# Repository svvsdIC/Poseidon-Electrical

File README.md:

# Poseidon-Electrical
Boards, files, and schematics for Poseidon
Notes:
  the Main Electronics Board is for the production version
  the Rapid_Prototype schematic is for the Rapid Prototype
  Turbidity sensor is a separate board used for the turbidity sensor.

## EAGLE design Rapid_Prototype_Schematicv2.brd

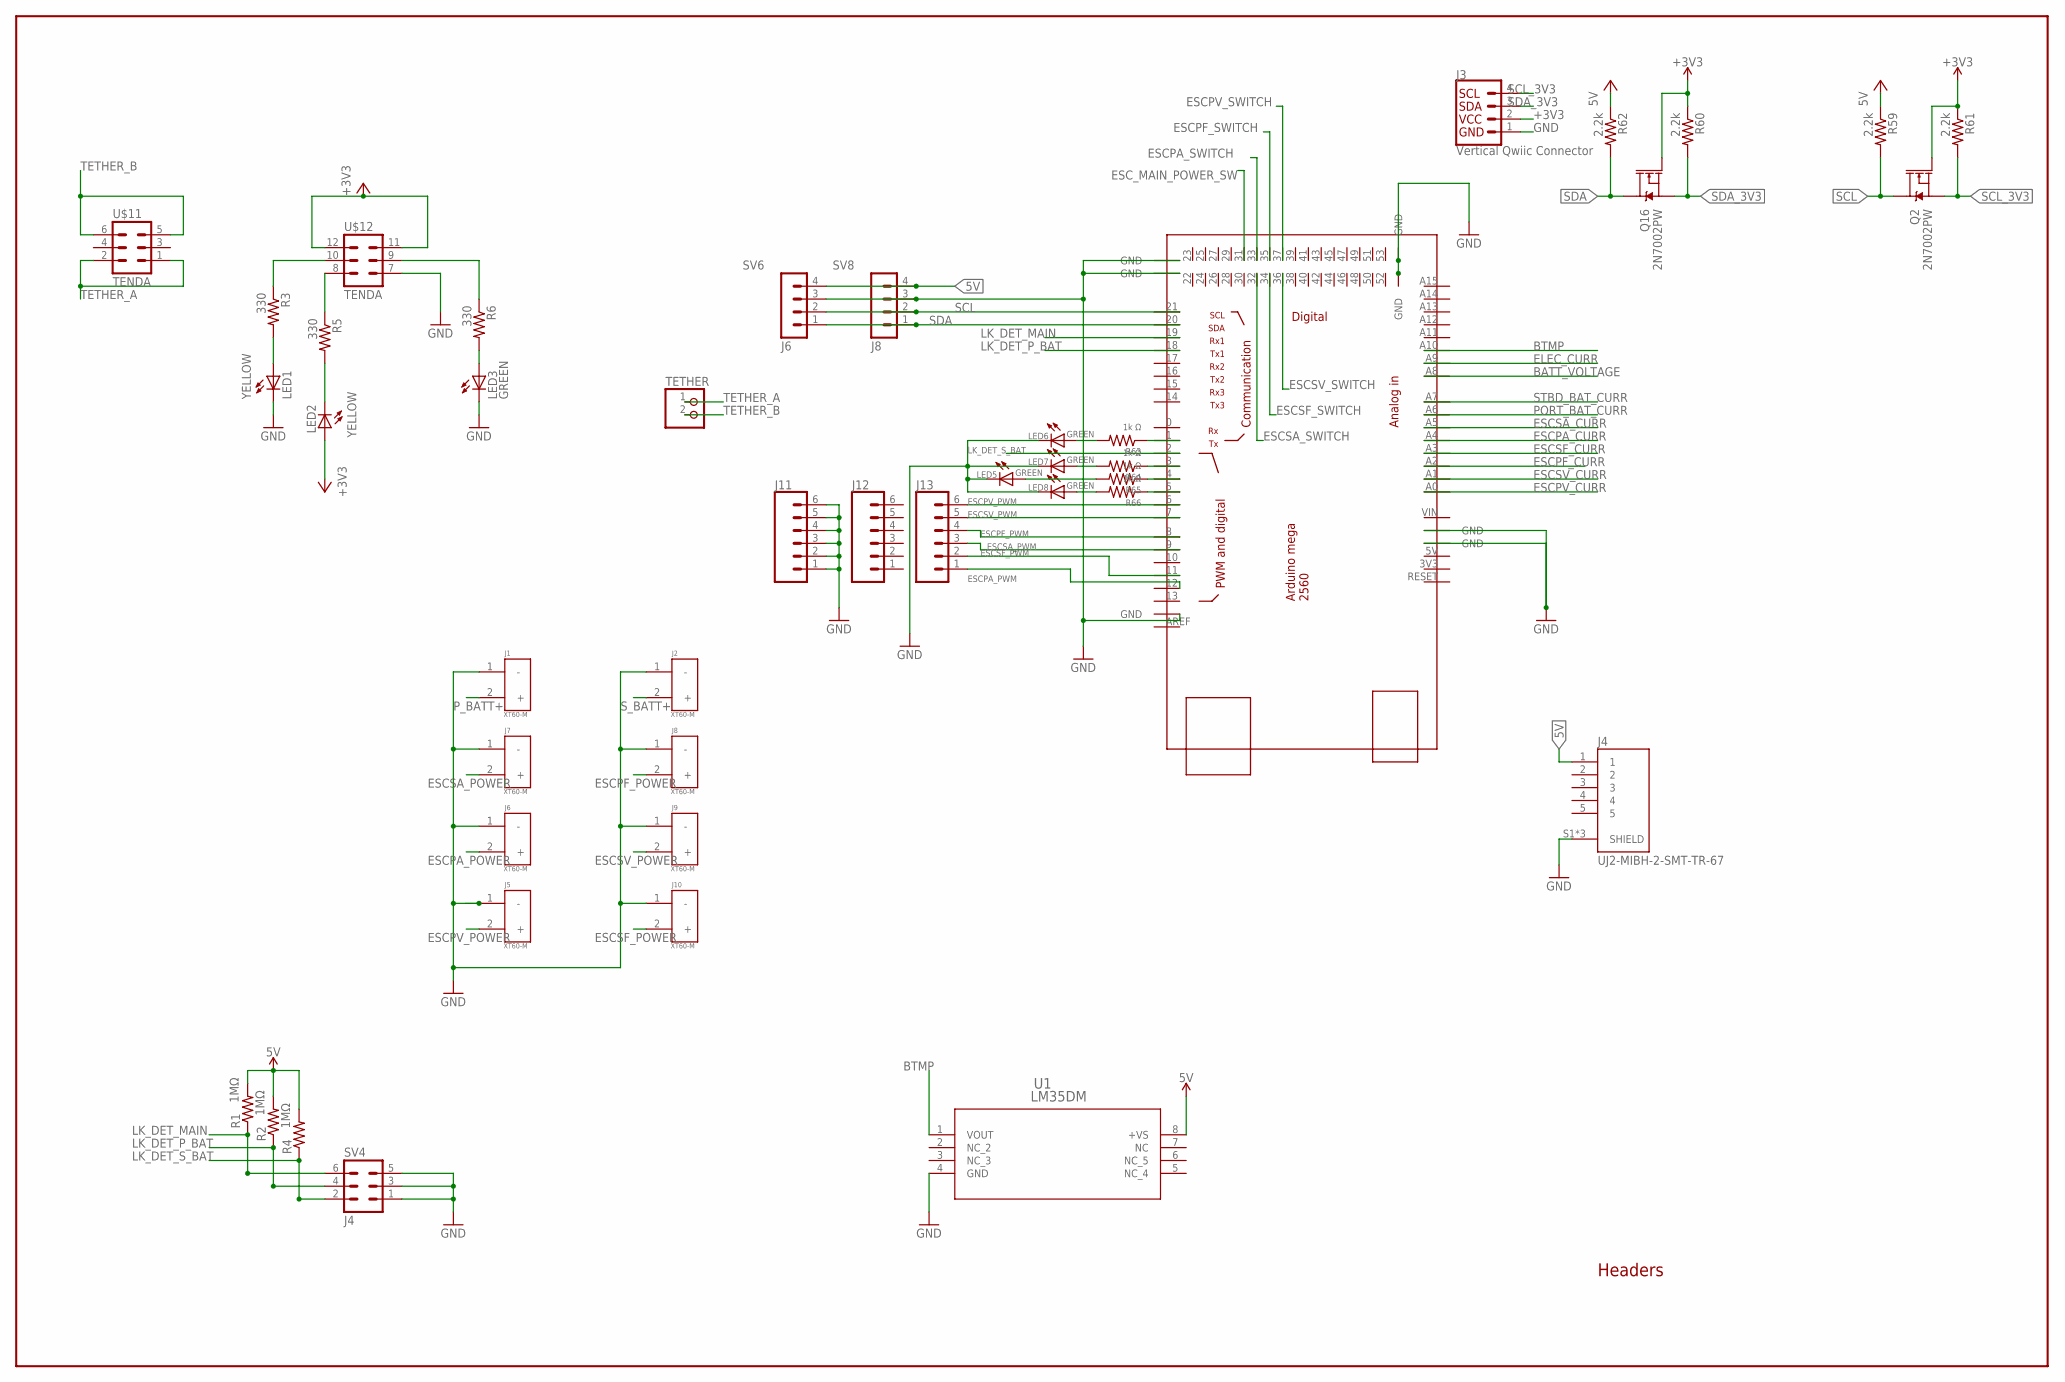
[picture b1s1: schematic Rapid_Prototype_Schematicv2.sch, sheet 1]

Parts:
$2_3_$_2020-06-04_21-52-10: MEGA_DEVICE; MEGAOUTLINE
J1, J2, J5, J6, J7, J8, J9, J10: XT60-M; AMASS_XT60-M
J3: Vertical Qwiic Connector; JST04_1MM_VERT
J4: UJ2-MIBH-2-SMT-TR-67; CUI_UJ2-MIBH-2-SMT-TR-67
J11, J12, J13: CONN_06SILK_FEMALE_PTH; 1X06
LED1, LED2: YELLOW; CHIPLED_0805
LED3, LED5, LED6, LED7, LED8: GREEN; CHIPLED_0805
Q2, Q16: 2N7002PW; SOT323
R1, R2, R4: 1MΩ; M0805
R3, R5, R6: 330; R0805
R59, R60, R61, R62: 2.2k; R0805
R63, R64, R65, R66: 1k Ω; M0805
SV4: J4; MA03-2
SV6: J6; MA04-1
SV8: J8; MA04-1
TETHER: PINHD-1X2; 1X02
U1: LM35DM; M08A
U$1: TENDA

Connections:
3.3V: Q2.1 (G), Q16.1 (G), R60.1, R61.1
5V: J4.1, R1.2, R2.2, R4.2, SV6.4, SV8.4, U1.8 (+VS); also elsewhere on the board
+3V3: J3.2, LED2.A, U$1.11 (5), U$1.12 (6); also elsewhere on the board
+5V: R59.1, R62.1
BATT_VOLTAGE: $2_3_$_2020-06-04_21-52-10.A8; also elsewhere on the board
BTMP: $2_3_$_2020-06-04_21-52-10.A10, U1.1 (VOUT)
ELEC_CURR: $2_3_$_2020-06-04_21-52-10.A9; also elsewhere on the board
ESCPA_CURR: $2_3_$_2020-06-04_21-52-10.A4; also elsewhere on the board
ESCPA_POWER: J6.2 (+); also elsewhere on the board
ESCPA_PWM: $2_3_$_2020-06-04_21-52-10.12, J13.1
ESCPA_SWITCH: $2_3_$_2020-06-04_21-52-10.33; also elsewhere on the board
ESCPF_CURR: $2_3_$_2020-06-04_21-52-10.A2; also elsewhere on the board
ESCPF_POWER: J8.2 (+); also elsewhere on the board
ESCPF_PWM: $2_3_$_2020-06-04_21-52-10.8, J13.4
ESCPF_SWITCH: $2_3_$_2020-06-04_21-52-10.35; also elsewhere on the board
ESCPV_CURR: $2_3_$_2020-06-04_21-52-10.A0; also elsewhere on the board
ESCPV_POWER: J5.2 (+); also elsewhere on the board
ESCPV_PWM: $2_3_$_2020-06-04_21-52-10.6, J13.6
ESCPV_SWITCH: $2_3_$_2020-06-04_21-52-10.37; also elsewhere on the board
ESCSA_CURR: $2_3_$_2020-06-04_21-52-10.A5; also elsewhere on the board
ESCSA_POWER: J7.2 (+); also elsewhere on the board
ESCSA_PWM: $2_3_$_2020-06-04_21-52-10.9, J13.3
ESCSA_SWITCH: $2_3_$_2020-06-04_21-52-10.32; also elsewhere on the board
ESCSF_CURR: $2_3_$_2020-06-04_21-52-10.A3; also elsewhere on the board
ESCSF_POWER: J10.2 (+); also elsewhere on the board
ESCSF_PWM: $2_3_$_2020-06-04_21-52-10.11, J13.2
ESCSF_SWITCH: $2_3_$_2020-06-04_21-52-10.34; also elsewhere on the board
ESCSV_CURR: $2_3_$_2020-06-04_21-52-10.A1; also elsewhere on the board
ESCSV_POWER: J9.2 (+); also elsewhere on the board
ESCSV_PWM: $2_3_$_2020-06-04_21-52-10.7, J13.5
ESCSV_SWITCH: $2_3_$_2020-06-04_21-52-10.36; also elsewhere on the board
ESC_MAIN_POWER_SW: $2_3_$_2020-06-04_21-52-10.31; also elsewhere on the board
GND: $2_3_$_2020-06-04_21-52-10.GND@1 (GND), $2_3_$_2020-06-04_21-52-10.GND@2 (GND), $2_3_$_2020-06-04_21-52-10.GND@3 (GND), $2_3_$_2020-06-04_21-52-10.GND@4 (GND), $2_3_$_2020-06-04_21-52-10.GND@5 (GND), $2_3_$_2020-06-04_21-52-10.GND@6 (GND), $2_3_$_2020-06-04_21-52-10.GND@7 (GND), J1.1 (-), J2.1 (-), J3.1, J4.S1 (SHIELD), J4.S2 (SHIELD), J4.S3 (SHIELD), J5.1 (-), J6.1 (-), J7.1 (-), J8.1 (-), J9.1 (-), J10.1 (-), J11.1, J11.2, J11.3, J11.4, J11.5, J11.6, LED1.C, LED3.C, LED5.C, LED6.C, LED7.C, LED8.C, SV4.1, SV4.3, SV4.5, SV6.3, SV8.3, U1.4 (GND), U$1.7 (1); also elsewhere on the board
LK_DET_MAIN: $2_3_$_2020-06-04_21-52-10.19, R1.1, SV4.6
LK_DET_P_BAT: $2_3_$_2020-06-04_21-52-10.18, R2.1, SV4.4
LK_DET_S_BAT: $2_3_$_2020-06-04_21-52-10.2, R4.1, SV4.2
unnamed: $2_3_$_2020-06-04_21-52-10.3, R64.1
unnamed: $2_3_$_2020-06-04_21-52-10.4, R65.1
unnamed: $2_3_$_2020-06-04_21-52-10.5, R66.1
unnamed: $2_3_$_2020-06-04_21-52-10.1, R63.1
unnamed: LED6.A, R63.2
unnamed: LED7.A, R64.2
unnamed: LED5.A, R65.2
unnamed: LED8.A, R66.2
unnamed: R3.1, U$1.10 (4)
unnamed: LED2.C, R5.2
unnamed: R5.1, U$1.8 (2)
unnamed: LED1.A, R3.2
unnamed: R6.1, U$1.9 (3)
unnamed: LED3.A, R6.2
PORT_BAT_CURR: $2_3_$_2020-06-04_21-52-10.A6; also elsewhere on the board
P_BATT+: J1.2 (+); also elsewhere on the board
SCL: $2_3_$_2020-06-04_21-52-10.21, Q2.3 (D), R59.2, SV6.2, SV8.2
SCL_3V3: J3.4, Q2.2 (S), R61.2
SDA: $2_3_$_2020-06-04_21-52-10.20, Q16.3 (D), R62.2, SV6.1, SV8.1
SDA_3V3: J3.3, Q16.2 (S), R60.2
STBD_BAT_CURR: $2_3_$_2020-06-04_21-52-10.A7; also elsewhere on the board
S_BATT+: J2.2 (+); also elsewhere on the board
TETHER_A: TETHER.1, U$1.1, U$1.2; also elsewhere on the board
TETHER_B: TETHER.2, U$1.5, U$1.6; also elsewhere on the board

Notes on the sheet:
Headers

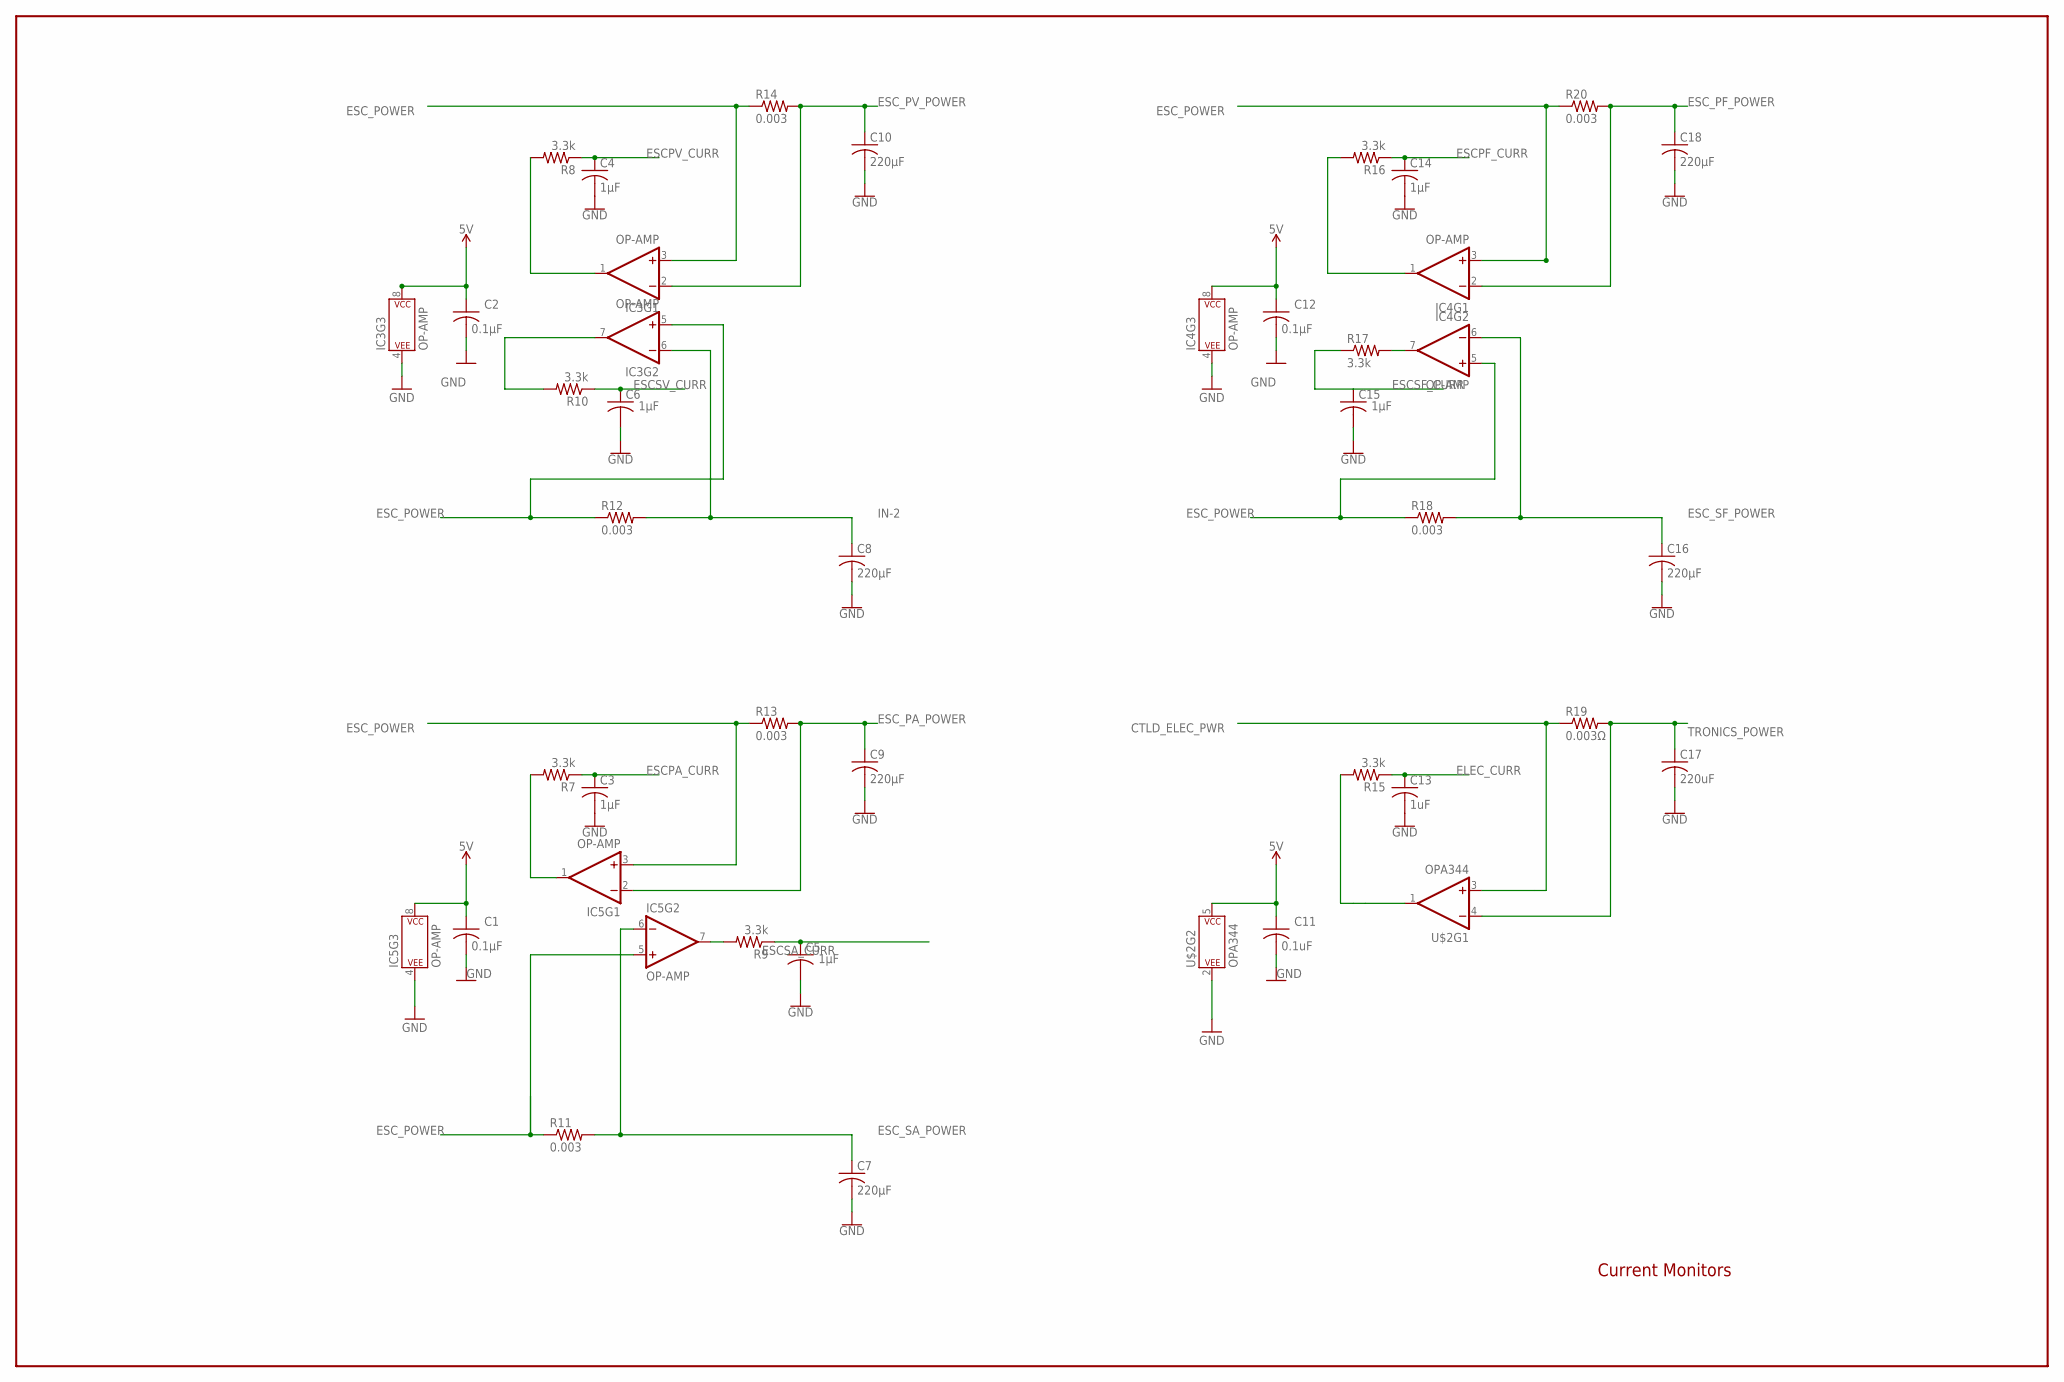
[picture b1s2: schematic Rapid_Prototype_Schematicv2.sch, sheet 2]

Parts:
C1, C2, C12: 0.1µF; C0603
C3, C4, C5, C6, C14, C15: 1µF; C0603
C7, C8, C9, C10, C16, C18: 220µF; 3.5MMCAP
C11: 0.1uF; C0603
C13: 1uF; C0805
C17: 220uF; 3.5MMCAP
IC3, IC4, IC5: OP-AMP; DIP08
R7, R8, R9, R10, R15, R16, R17: 3.3k; R0603
R11, R12, R13, R14, R18, R20: 0.003; R1206
R19: 0.003Ω; R1206
U$2: OPA344; SOT23-5

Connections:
5V: C1.1, C2.1, C11.1, C12.1, IC3.8 (P$V+), IC4.8 (P$V+), IC5.8 (P$V+), U$2.5 (P$V+); also elsewhere on the board
CTLD_ELEC_PWR: R19.1, U$2.3 (+IN); also elsewhere on the board
ELEC_CURR: C13.1, R15.1; also elsewhere on the board
ESCPA_CURR: C3.1, R7.1; also elsewhere on the board
ESCPF_CURR: C14.1, R16.1; also elsewhere on the board
ESCPV_CURR: C4.1, R8.1; also elsewhere on the board
ESCSA_CURR: C5.1, R9.1; also elsewhere on the board
ESCSF_CURR: C15.1, R17.1; also elsewhere on the board
ESCSV_CURR: C6.1, R10.1; also elsewhere on the board
ESC_PA_POWER: C9.1, IC5.2 (-IN), R13.2; also elsewhere on the board
ESC_PF_POWER: C18.1, IC4.2 (-IN), R20.2; also elsewhere on the board
ESC_POWER: IC3.3 (+IN), IC3.5 (+IN), IC4.3 (+IN), IC4.5 (+IN), IC5.3 (+IN), IC5.5 (+IN), R11.1, R12.1, R13.1, R14.1, R18.1, R20.1; also elsewhere on the board
ESC_PV_POWER: C10.1, IC3.2 (-IN), R14.2; also elsewhere on the board
ESC_SA_POWER: C7.1, IC5.6 (-IN), R11.2; also elsewhere on the board
ESC_SF_POWER: C16.1, IC4.6 (-IN), R18.2; also elsewhere on the board
GND: C1.2, C2.2, C3.2, C4.2, C5.2, C6.2, C7.2, C8.2, C9.2, C10.2, C11.2, C12.2, C13.2, C14.2, C15.2, C16.2, C17.2, C18.2, IC3.4 (P$V-), IC4.4 (P$V-), IC5.4 (P$V-), U$2.2 (P$V-); also elsewhere on the board
IN-2: C8.1, IC3.6 (-IN), R12.2
unnamed: IC4.1 (OUT), R16.2
unnamed: IC4.7 (OUT), R17.2
unnamed: IC5.1 (OUT), R7.2
unnamed: IC5.7 (OUT), R9.2
unnamed: R15.2, U$2.1 (OUT)
O: IC3.1 (OUT), R8.2
O2: IC3.7 (OUT), R10.2
TRONICS_POWER: C17.1, R19.2, U$2.4 (-IN); also elsewhere on the board

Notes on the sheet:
Current Monitors

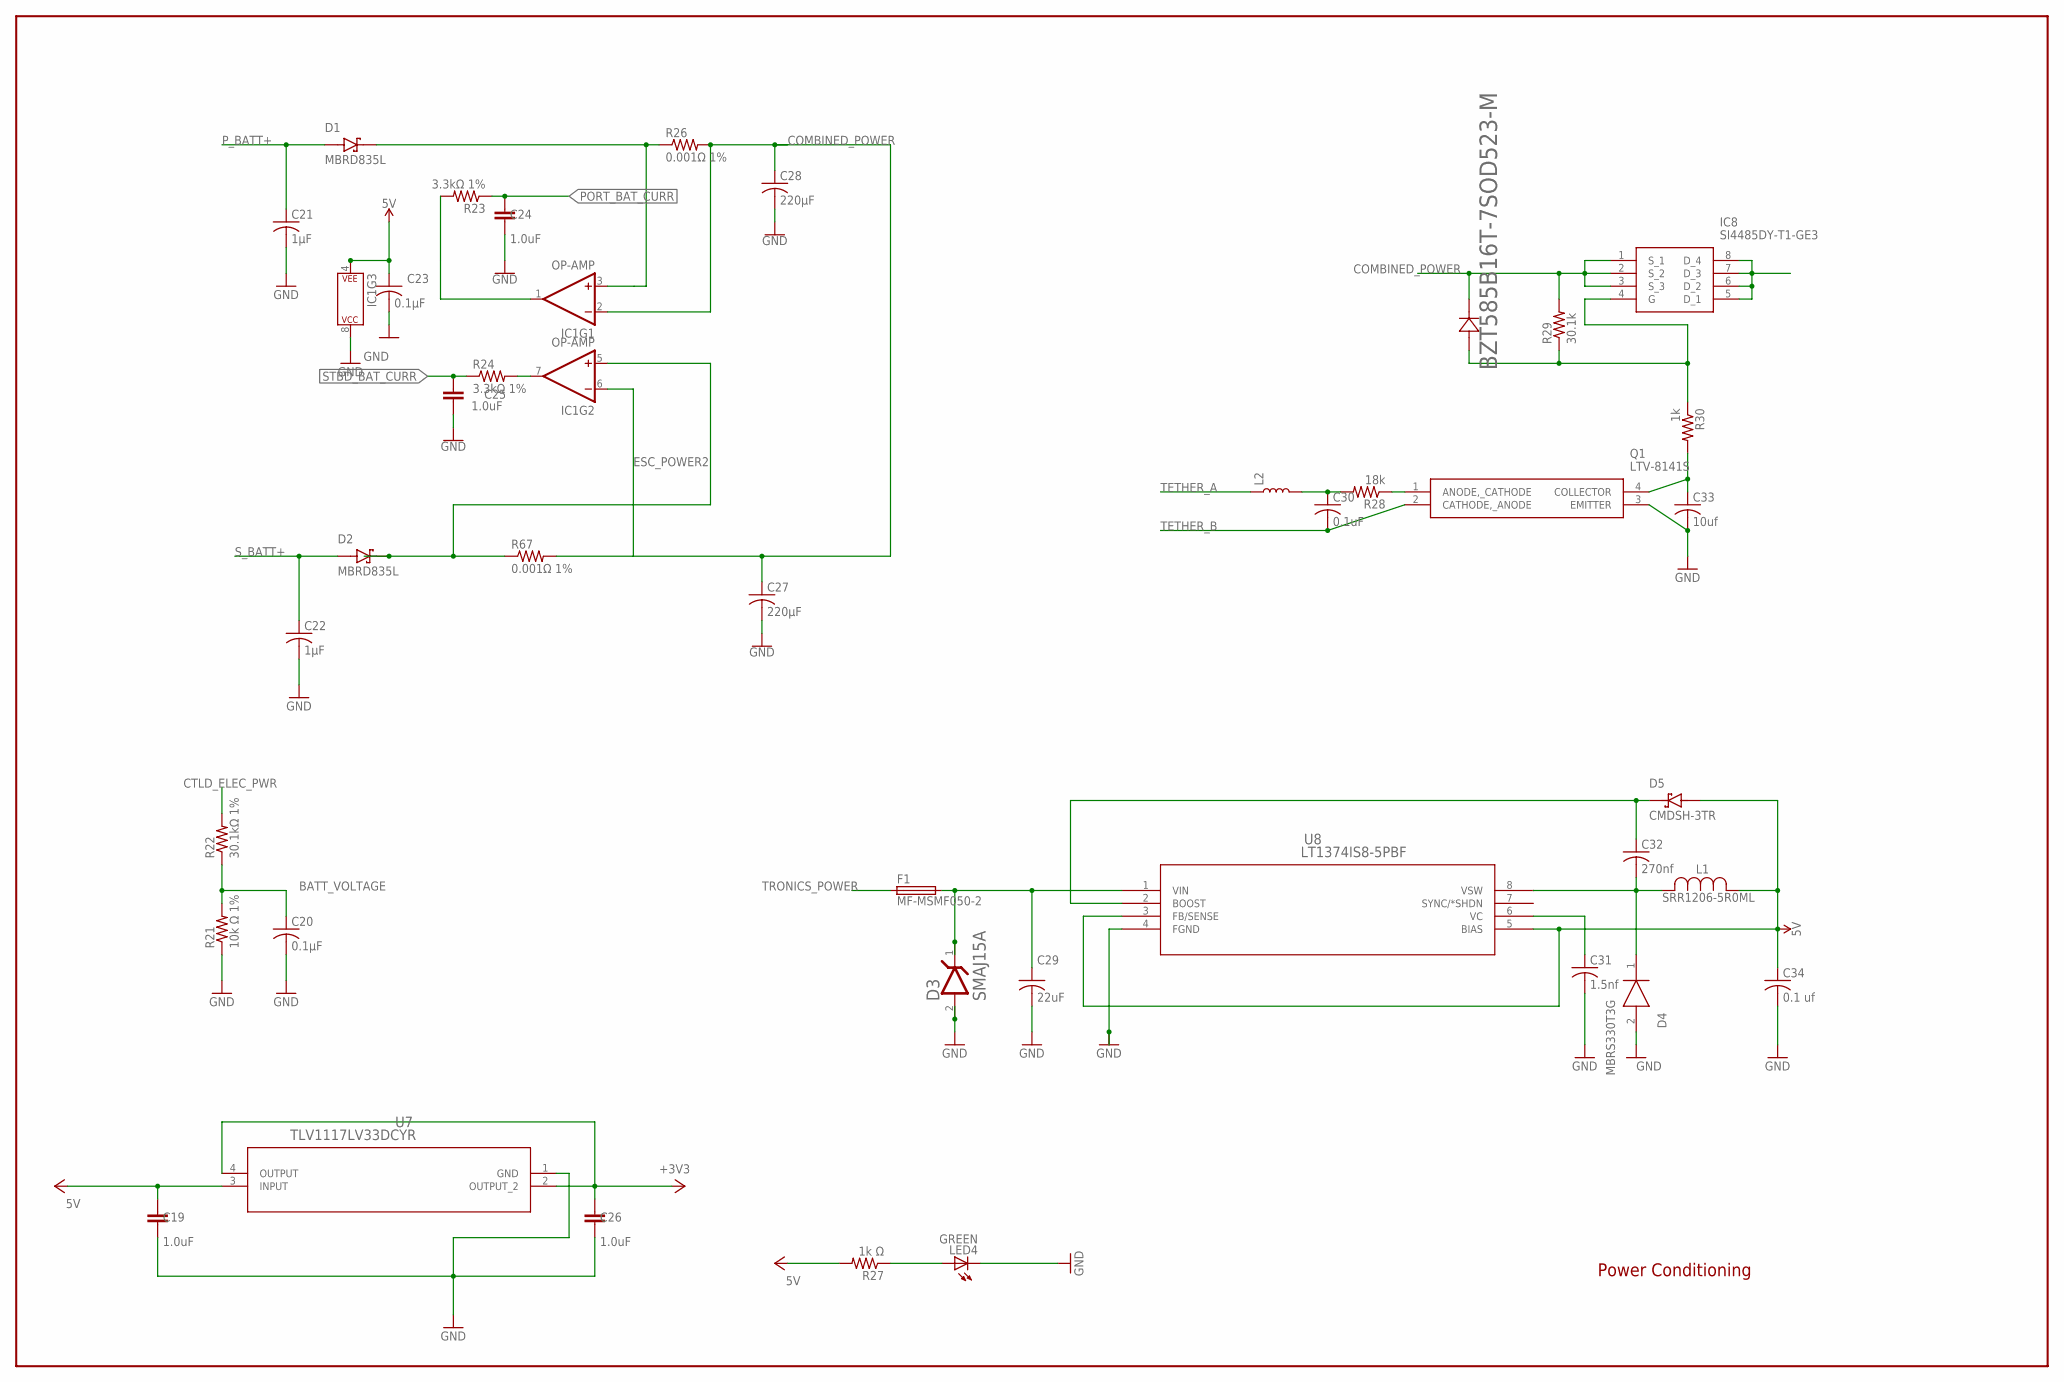
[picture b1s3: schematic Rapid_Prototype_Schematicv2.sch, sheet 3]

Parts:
C19, C24, C25, C26: 1.0uF; 0603
C20, C23: 0.1µF; C0603
C21, C22: 1µF; C0603
C27, C28: 220µF; 3.5MMCAP
C29: 22uF; C1206
C30: 0.1uF; C0603
C31: 1.5nf; C1206
C32: 270nf; C0603
C33: 10uf; C0603
C34: 0.1 uf; C0603
CR1: BZT585B16T-7SOD523-M; SOD523-M
D1, D2: MBRD835L; DPAK229P990X238-3N
D3: BOURNS-INC.---SMAJ15A_BOURNS_INC._SMAJ15ABOURNS_I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; BOURNS-INC.---SMAJ15A_BOURNS_INC._SMAJ15A_0
D4: MBRS330T3G; DIOM7958X256N
D5: CMDSH-3TR; SOD2512X110N
F1: MF-MSMF050-2; FUSM1812X02
IC1: OP-AMP; DIP08
IC8: SI4485DY-T1-GE3; SOIC127P600X175-8N
L1: SRR1206-5R0ML; IND_BOURNS_SRR1240
L2: INDUCTOR; XFL4020
LED4: GREEN; CHIPLED_0805
Q1: LTV-8141S; SOP254P1016X460-4N
R21: 10k Ω 1%; M0805
R22: 30.1kΩ 1%; M0805
R23, R24: 3.3kΩ 1%; R0603
R26, R67: 0.001Ω 1%; R2512
R27: 1k Ω; M0805
R28: 18k; M0805
R29: 30.1k; M0805
R30: 1k; M0805
U7: TLV1117LV33DCYR; DCY4
U8: LT1374IS8-5PBF; SO-8_S

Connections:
5V: C19.1, C23.1, C34.1, D5.A, IC1.4 (P$V-), L1.1, R27.2, U7.3 (INPUT), U8.3 (FB/SENSE), U8.5 (BIAS); also elsewhere on the board
+3V3: C26.1, U7.2 (OUTPUT_2), U7.4 (OUTPUT); also elsewhere on the board
BATT_VOLTAGE: C20.1, R21.2, R22.1; also elsewhere on the board
COMBINED_POWER: C27.1, C28.1, CR1.1, IC1.2 (-IN), IC1.6 (-IN), IC8.1 (S_1), IC8.2 (S_2), IC8.3 (S_3), R26.2, R29.2, R67.2; also elsewhere on the board
CTLD_ELEC_PWR: IC8.5 (D_1), IC8.6 (D_2), IC8.7 (D_3), IC8.8 (D_4), R22.2; also elsewhere on the board
ESC_POWER1: D1.4 (K), IC1.3 (+IN), R26.1
ESC_POWER2: D2.4 (K), IC1.5 (+IN), R67.1
GND: C19.2, C20.2, C21.2, C22.2, C23.2, C24.2, C25.2, C26.2, C27.2, C28.2, C29.2, C31.2, C33.2, C34.2, D3.2 (ANODE), D4.2 (A), IC1.8 (P$V+), LED4.C, Q1.3 (EMITTER), R21.1, U7.1 (GND), U8.4 (FGND); also elsewhere on the board
unnamed: C32.2, D4.1 (K), L1.2, U8.8 (VSW)
unnamed: C31.1, U8.6 (VC)
unnamed: Q1.1 (ANODE,_CATHODE), R28.1
unnamed: IC1.1 (OUT), R23.2
unnamed: IC1.7 (OUT), R24.2
unnamed: C29.1, D3.1 (CATHODE), F1.2, U8.1 (VIN)
unnamed: C32.1, D5.C, U8.2 (BOOST)
unnamed: LED4.A, R27.1
unnamed: CR1.2, IC8.4 (G), R29.1, R30.1
unnamed: C33.1, Q1.4 (COLLECTOR), R30.2
unnamed: C30.1, L2.P$2 (2), R28.2
PORT_BAT_CURR: C24.1, R23.1; also elsewhere on the board
P_BATT+: C21.1, D1.1 (A), D1.3 (A); also elsewhere on the board
STBD_BAT_CURR: C25.1, R24.1; also elsewhere on the board
S_BATT+: C22.1, D2.1 (A), D2.3 (A); also elsewhere on the board
TETHER_A: L2.P$1 (1); also elsewhere on the board
TETHER_B: C30.2, Q1.2 (CATHODE,_ANODE); also elsewhere on the board
TRONICS_POWER: F1.1; also elsewhere on the board

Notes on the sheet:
Power Conditioning

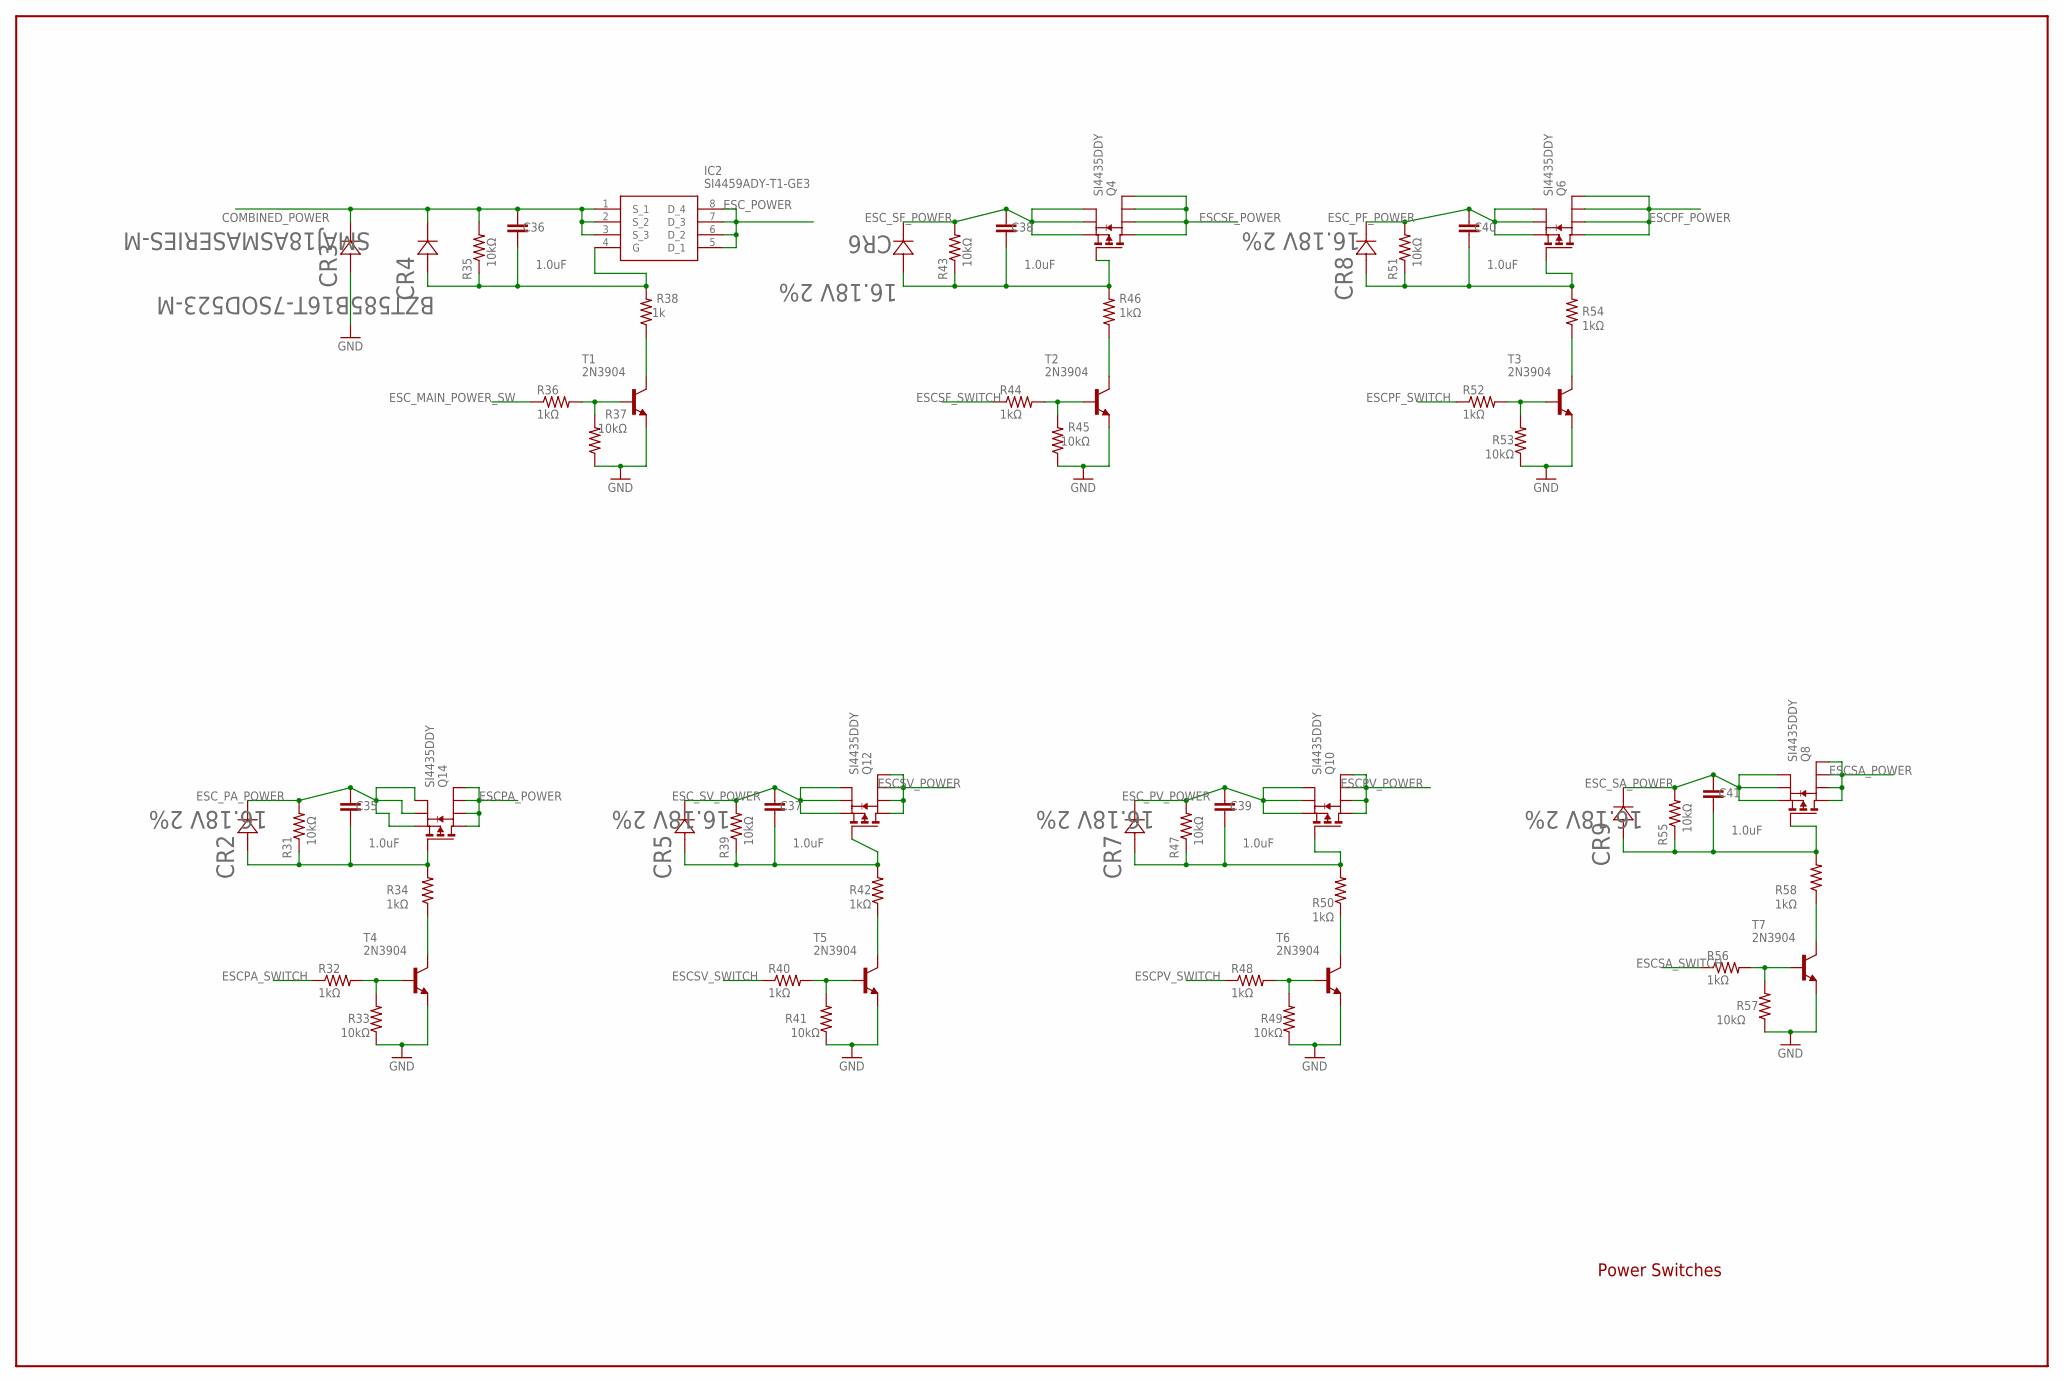
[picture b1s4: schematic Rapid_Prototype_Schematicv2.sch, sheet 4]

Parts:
C35, C36, C37, C38, C39, C40, C41: 1.0uF; 0603
CR2, CR5, CR6, CR7, CR8, CR9: 16.18V 2%; SOD523-M
CR3: SMAJ18ASMASERIES-M; SMASERIES-M
CR4: BZT585B16T-7SOD523-M; SOD523-M
IC2: SI4459ADY-T1-GE3; SOIC127P600X175-8N
Q4, Q6, Q8, Q10, Q12, Q14: SI4435DDY; SO-8
R31, R33, R35, R37, R39, R41, R43, R45, R47, R49, R51, R53, R55, R57: 10kΩ; R0603
R32, R34, R36, R40, R42, R44, R46, R48, R50, R52, R54, R56, R58: 1kΩ; R0603
R38: 1k; R0603
T1, T2, T3, T4, T5, T6, T7: 2N3904; TO92

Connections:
COMBINED_POWER: C36.1, CR3.1, CR4.1, IC2.1 (S_1), IC2.2 (S_2), IC2.3 (S_3), R35.2; also elsewhere on the board
ESCPA_POWER: Q14.5 (D), Q14.6 (D), Q14.7 (D), Q14.8 (D); also elsewhere on the board
ESCPA_SWITCH: R32.1; also elsewhere on the board
ESCPF_POWER: Q6.5 (D), Q6.6 (D), Q6.7 (D), Q6.8 (D); also elsewhere on the board
ESCPF_SWITCH: R52.1; also elsewhere on the board
ESCPV_POWER: Q10.5 (D), Q10.6 (D), Q10.7 (D), Q10.8 (D); also elsewhere on the board
ESCPV_SWITCH: R48.1; also elsewhere on the board
ESCSA_POWER: Q8.5 (D), Q8.6 (D), Q8.7 (D), Q8.8 (D); also elsewhere on the board
ESCSA_SWITCH: R56.1; also elsewhere on the board
ESCSF_POWER: Q4.5 (D), Q4.6 (D), Q4.7 (D), Q4.8 (D); also elsewhere on the board
ESCSF_SWITCH: R44.1; also elsewhere on the board
ESCSV_POWER: Q12.5 (D), Q12.6 (D), Q12.7 (D), Q12.8 (D); also elsewhere on the board
ESCSV_SWITCH: R40.1; also elsewhere on the board
ESC_MAIN_POWER_SW: R36.1; also elsewhere on the board
ESC_PA_POWER: C35.1, CR2.1, Q14.1 (S), Q14.2 (S), Q14.3 (S), R31.2; also elsewhere on the board
ESC_PF_POWER: C40.1, CR8.1, Q6.1 (S), Q6.2 (S), Q6.3 (S), R51.2; also elsewhere on the board
ESC_POWER: IC2.5 (D_1), IC2.6 (D_2), IC2.7 (D_3), IC2.8 (D_4); also elsewhere on the board
ESC_PV_POWER: C39.1, CR7.1, Q10.1 (S), Q10.2 (S), Q10.3 (S), R47.2; also elsewhere on the board
ESC_SA_POWER: C41.1, CR9.1, Q8.1 (S), Q8.2 (S), Q8.3 (S), R55.2; also elsewhere on the board
ESC_SF_POWER: C38.1, CR6.1, Q4.1 (S), Q4.2 (S), Q4.3 (S), R43.2; also elsewhere on the board
ESC_SV_POWER: C37.1, CR5.1, Q12.1 (S), Q12.2 (S), Q12.3 (S), R39.2
GND: CR3.2, R33.1, R37.1, R41.1, R45.1, R49.1, R53.1, R57.1, T1.3 (E), T2.3 (E), T3.3 (E), T4.3 (E), T5.3 (E), T6.3 (E), T7.3 (E); also elsewhere on the board
unnamed: C36.2, CR4.2, IC2.4 (G), R35.1, R38.2
unnamed: R32.2, R33.2, T4.2 (B)
unnamed: C40.2, CR8.2, Q6.4 (G), R51.1, R54.2
unnamed: C35.2, CR2.2, Q14.4 (G), R31.1, R34.2
unnamed: R38.1, T1.1 (C)
unnamed: R36.2, R37.2, T1.2 (B)
unnamed: R34.1, T4.1 (C)
unnamed: C37.2, CR5.2, Q12.4 (G), R39.1, R42.2
unnamed: R40.2, R41.2, T5.2 (B)
unnamed: R42.1, T5.1 (C)
unnamed: C39.2, CR7.2, Q10.4 (G), R47.1, R50.2
unnamed: R48.2, R49.2, T6.2 (B)
unnamed: R50.1, T6.1 (C)
unnamed: C41.2, CR9.2, Q8.4 (G), R55.1, R58.2
unnamed: R56.2, R57.2, T7.2 (B)
unnamed: R58.1, T7.1 (C)
unnamed: R52.2, R53.2, T3.2 (B)
unnamed: R54.1, T3.1 (C)
unnamed: C38.2, CR6.2, Q4.4 (G), R43.1, R46.2
unnamed: R44.2, R45.2, T2.2 (B)
unnamed: R46.1, T2.1 (C)

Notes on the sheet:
Power Switches

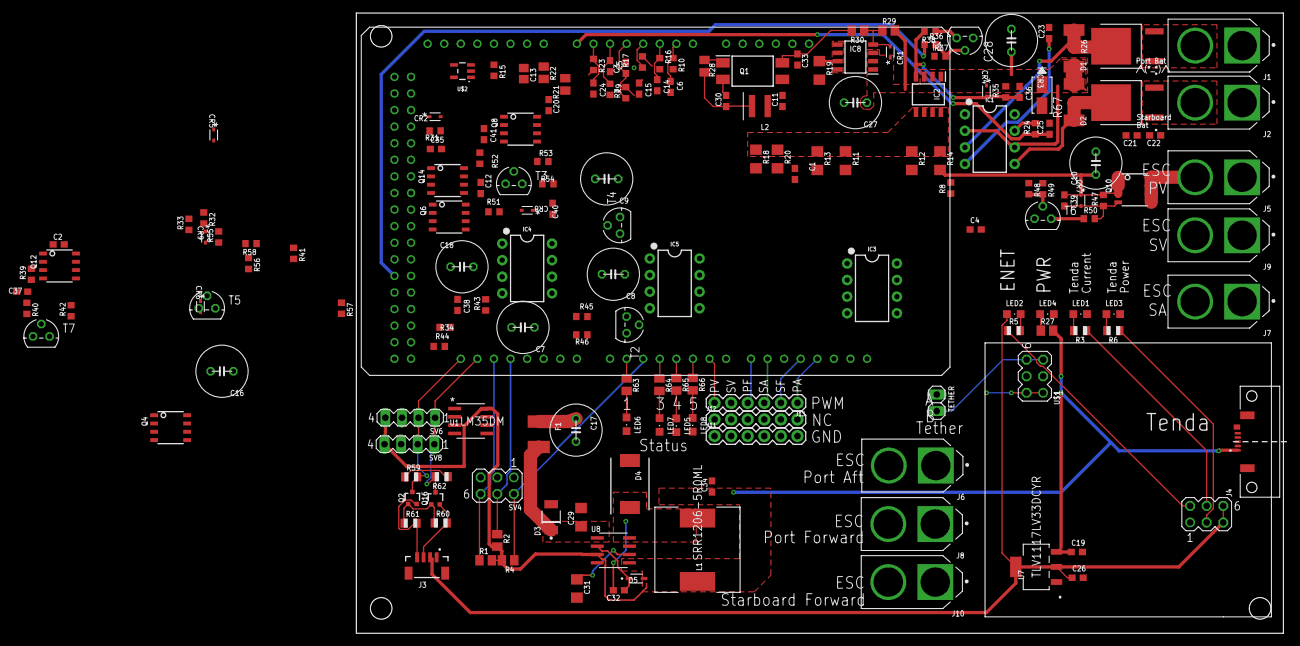
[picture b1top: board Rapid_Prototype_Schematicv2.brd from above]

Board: 2 copper layers, 142.5 x 95.0 mm, 177 parts (0 on the bottom side), 112 nets.

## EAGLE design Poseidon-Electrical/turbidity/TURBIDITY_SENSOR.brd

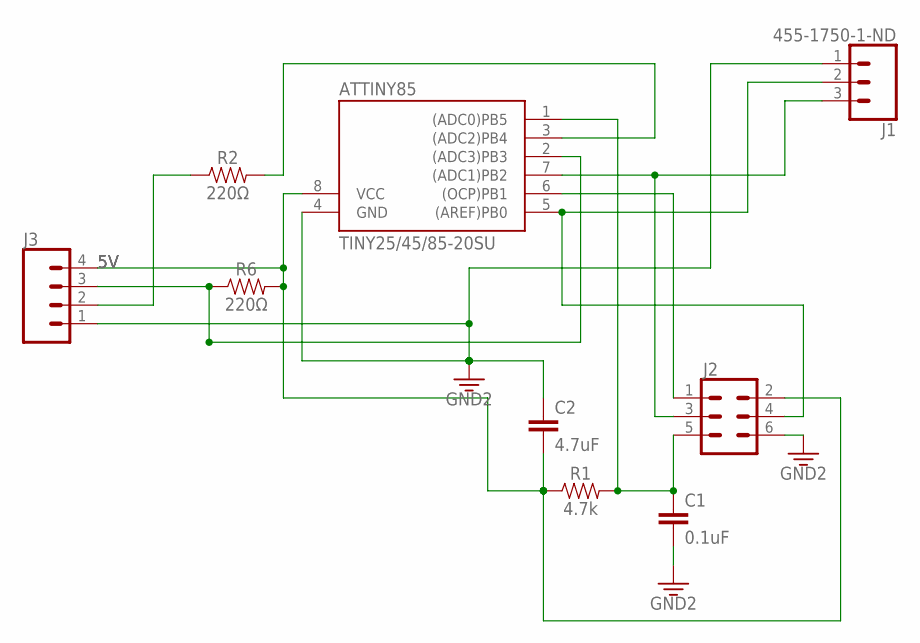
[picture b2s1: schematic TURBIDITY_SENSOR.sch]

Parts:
ATTINY85: TINY25/45/85-20SU; SOIC8
C1: 0.1uF; 0603
C2: 4.7uF; 1206
J1: 455-1750-1-ND; 1X03
J2: CONN_03X22X3_SILK_MALE_PTH; 2X3
J3: CONN_04; 1X04
R1: 4.7k; 0603
R2, R6: 220Ω; 0603

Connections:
5V: ATTINY85.8 (VCC), C2.2, J2.2, J3.4, R1.1, R6.2
DETECT: ATTINY85.2 ((ADC3)PB3), J3.3, R6.1
EMIT: ATTINY85.3 ((ADC2)PB4), R2.2
EMIT_OUT: J3.2, R2.1
GND: ATTINY85.4 (GND), C1.2, C2.1, J1.1, J2.6, J3.1
MISO: ATTINY85.6 ((OCP)PB1), J2.1
MOSI: ATTINY85.5 ((AREF)PB0), J1.2, J2.4
RESET: ATTINY85.1 ((ADC0)PB5), C1.1, J2.5, R1.2
SCK: ATTINY85.7 ((ADC1)PB2), J1.3, J2.3

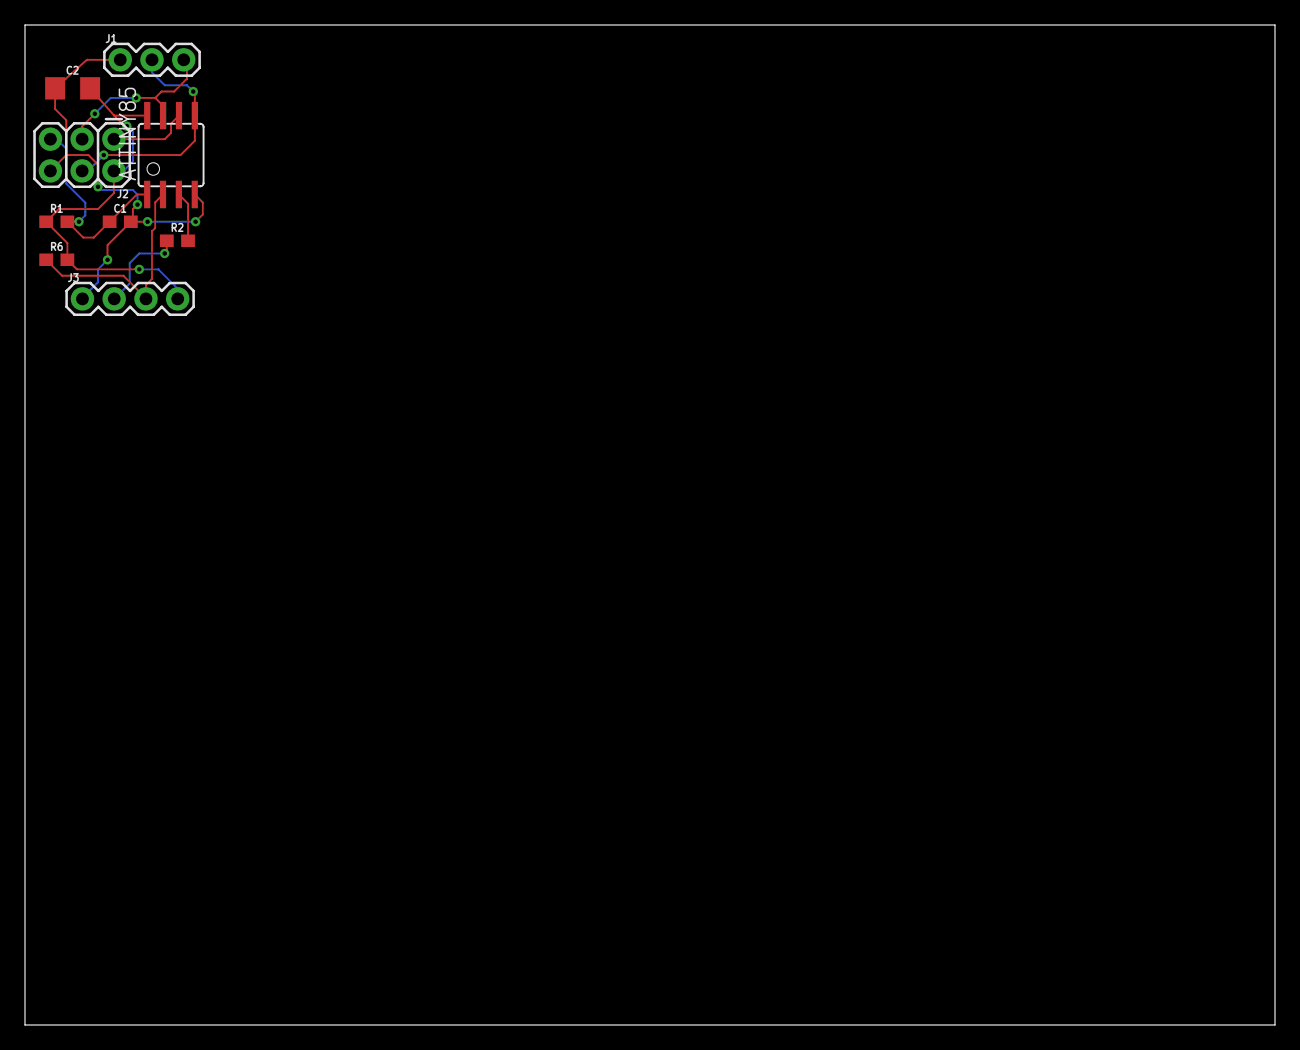
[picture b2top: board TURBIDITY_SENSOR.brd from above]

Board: 2 copper layers, 100.0 x 80.0 mm, 9 parts (0 on the bottom side), 9 nets.

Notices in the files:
parts and their libraries:
SparkFun-Capacitors: Licensing: Creative Commons ShareAlike 4.0 International - https://creativecommons.org/licenses/by-sa/4.0
